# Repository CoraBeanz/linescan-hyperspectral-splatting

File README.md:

<h3 align="center">A homebuilt pushbroom spectrograph rides a robot arm, and the 3D Gaussian splat it trains stores a full 500–950 nm spectrum in every Gaussian instead of an RGB color.</h3>

<p align="center">

</p>

<p align="center">
  <a href="#how-it-works"><b>How it works</b></a> ·
  <a href="#the-rig"><b>The rig</b></a> ·
  <a href="#cad-model"><b>CAD model</b></a> ·
  <a href="#optical-path"><b>Optical path</b></a> ·
  <a href="#optiland-model"><b>Optiland model</b></a> ·
  <a href="#software"><b>Software</b></a> ·
  <a href="#reconstruction"><b>Reconstruction</b></a> ·
  <a href="#roadmap"><b>Roadmap</b></a> ·
  <a href="docs/manual/README.md"><b>User's manual</b></a> ·
  <a href="docs/parts_list_and_design.md"><b>Parts list</b></a>
</p>

## How it works

A hyperspectral camera records a whole spectrum at every pixel instead of three color channels, which shows things RGB can't, like the sharp rise in a leaf's reflectance just past red. This one is built from M12 board lenses, grating film and a Raspberry Pi camera sensor, for under $500 in optics and scanner parts.

| 1 · Pick a viewpoint | 2 · Sweep the slit | 3 · Train the splat |
|---|---|---|
| The SO-101 arm carries the scanner head to a pose and holds still. Its joint angles, through the robot model, give that pose. | A NEMA 8 stepper turns the scan mirror two microsteps per frame. Each frame is one line of the object by its spectrum, and a 107-line sweep covers about 64 × 43 mm. | Every scan line is a training sample. A C++/CUDA renderer draws the splat through a line-camera model at that line's pose and compares it with the measured line. |

## The rig

<table>
  <tr>
    <td width="42%" valign="top">
      
      <br><sub>SO-101 follower arm. Photo: <a href="https://github.com/TheRobotStudio/SO-ARM100">TheRobotStudio/SO-ARM100</a>, Apache-2.0.</sub>
    </td>
    <td valign="top">

**Arm.** An [SO-101](https://huggingface.co/docs/lerobot/so101) follower from [LeRobot](https://github.com/huggingface/lerobot), with six STS3215 servos. It only sets the viewpoint, then holds still while the mirror scans.

**Scanner head.** The spectrograph below, plus a first-surface scan mirror on a 60 g NEMA 8 stepper. A TMC2209 driver runs it at 1/32 microstepping from an ESP32, which takes plain-text commands from the Jetson over USB serial.

**Pose.** The arm's joint readings give the head's pose for every line. A Pi NoIR camera on the head reads a printed ChArUco board once, in the [head calibration](calibration/headcal/README.md), to measure where the head really sits on the wrist.

**Light.** Halogen lamps, because LEDs give almost nothing past 700 nm.

**Compute.** A Jetson Nano for capture, the calibration warp and the CUDA splat renderer.

  </td>
  </tr>
</table>

## CAD model

<table>
  <tr>
    <td width="50%"></td>
    <td width="50%"></td>
  </tr>
  <tr>
    <td><sub>The head from below: scan window and hood, pose camera, NEMA 8 stepper, wrist puck.</sub></td>
    <td><sub>Lid and stepper hidden to show the optical train.</sub></td>
  </tr>
</table>

The whole rig is a parametric [FreeCAD model](cad/). One script builds the SO-101 from its URDF, reads the optical spacings from the Optiland model, and wraps the optics in a printable PETG housing that slides onto a puck on the wrist-roll servo. It checks the parts for clashes, the mirror's full turn and the wrist's clearance, and works out the servo load: the 187 g head needs 75% of the shoulder servo's stall torque with the arm stretched out level, and 18% in the folded scanning pose above. The STLs and assembly steps are in [`cad/`](cad/).

## Optical path

A 16 mm f/4 objective images the object onto a 50 µm slit, so the instrument sees one line at a time. A field lens right behind the slit steers every point of that line toward the camera. A 25 mm lens, used backward, collimates the light, and a 500 lines/mm transmission grating fans it out by wavelength. A 12 mm f/2 lens, tilted 22° to the first diffraction order, refocuses the fan onto an IMX219 NoIR sensor, so each frame is one line of the object by its spectrum. A 500 nm long-pass filter in front keeps second-order light off the near-infrared end. Why each part is there: [final optical train](docs/parts_list_and_design.md#2-final-optical-train-config-c).

### What the camera sees

Each frame is the scan line (vertical) by its spectrum (horizontal), at about 5.8 px per nm. Spectral lines bow slightly across the frame (smile, up to about 33 px at the line ends) and the line length shifts a little with wavelength (keystone, about 11 px). Both get calibrated once with lamp lines and removed by a warp.

## Optiland model

[`optics/spectrograph_model.py`](optics/spectrograph_model.py) builds the whole train in [Optiland](https://github.com/HarrisonKramer/optiland) with ideal thin lenses and traces it. Tracing changed the design twice: the stock Pi NoIR lens was far too small to catch the collimated beam, and without a field lens most of the light from the ends of the line missed the camera lens.

| Config (ideal lenses) | Light at line center | Light at line ends | Dispersion | Spectral resolution | Pixels along the line |
|---|---|---|---|---|---|
| A: stock Pi NoIR v2 lens | 8% | 0% | 1.5 px/nm | 3.7 nm | 543 |
| B: M12 IMX219 + 12 mm f/2 lens | 92–100% | 12–14% | 5.8 px/nm | 3.7 nm | 2,143 |
| **C: B + 18 mm field lens** | **100%** | **98–99%** | **5.8 px/nm** | **4.1 nm** | **2,204** |

Resolution is geometric, with perfect lenses: the slit image's width over the dispersion. For A and B it is the paraxial estimate. For C it is traced through the grating, which widens the slit image 1.08× as the beam leaves at 22°, and the field lens adds 1.03×. The parts that were bought trace to 4.1 nm as [`cad/`](cad/README.md) builds the head, with the field lens curved side to the slit (config E); turned the other way it would be 5.4 nm (config D, [design notes](docs/parts_list_and_design.md#with-the-parts-that-were-bought-configs-d-and-e)). Real M12 lenses will likely land around 5–8 nm. More in the [modeling notes](docs/parts_list_and_design.md#5-modeling-notes-and-limits).

```bash
pip install optiland                   # tested with 0.6.2
python optics/spectrograph_model.py    # prints the table, writes optics/model_output/
python optics/readme_figures.py        # redraws the Optiland figures in docs/img/
```

Full output: [`optics/model_output/results.txt`](optics/model_output/results.txt) and the [ray layouts](optics/model_output/).

## Software

<p align="center">
  <img src="docs/img/software.svg" width="100%" alt="Block diagram of the code. The scan-mirror firmware on the ESP32 talks to the ROS 2 scan arm on the Jetson Nano over USB serial. The camera's frames go to the ROS 2 side during scans and to the calibration kit as lamp frames, and the calibration kit gives the ROS 2 side a wavelength map and a warp. The ROS 2 side passes lines with poses to the line-camera splat, which stores a spectrum in every Gaussian, and the splat goes to a browser viewer as one file. A band at the bottom shows the Optiland and FreeCAD models the code takes its numbers from, and the simulator that renders whole scans from them to test on.">
</p>

The rig isn't built yet, so every module is written and tested against simulated hardware: the firmware on a simulated rig, the ROS 2 side on a fake servo bus and a simulated mirror, the calibration kit on lamp frames rendered through the Optiland model, and the splat on a synthetic scan with known poses. The [instrument simulator](sim/) ties them together: a digital twin of the whole rig that renders complete scan sessions, raw frames and logged poses, from a scene whose spectra and geometry are known. GitHub Actions runs each module's checks on every pull request that touches it.

| Module | What CI checks | Status |
|---|---|---|
| [Scan-mirror firmware](firmware/) | Unit tests on a simulated rig, again under AddressSanitizer and UndefinedBehaviorSanitizer, and the ESP32 build |  |
| [ROS 2 scan arm](ros2/) | `colcon build` and `colcon test` in a ROS 2 Humble container, up to a two-viewpoint scan on mock hardware |  |
| [Calibration kit](calibration/) | The self-test and unit tests on Python 3.10 and 3.13, and the Jetson's capture commands on Python 3.6 and numpy 1.13 against a stand-in camera |  |
| [Line-camera splat](splat/) | CPU build and unit tests, and a small synthetic scan trained end to end; the CUDA build with CUDA 13.4 for a desktop GPU (CI has no GPU, so the GPU tests skip there) |  |
| [Jetson Nano build](jetson/README.md) | The renderer and trainer built with the Nano's CUDA 10.2 and gcc 7.5 for sm_53, every kernel checked against the Nano's registers and shared memory, and the tests on arm64 Ubuntu 18.04 |  |
| [Splat viewer](viewer/) | The page's file reader, colour weights, spectra and WebGL2 image against the C++ renderer, then the page itself at a desktop and a phone size, in headless Chromium |  |
| [GitHub Pages site](https://corabeanz.github.io/linescan-hyperspectral-splatting/) | Builds the front page and the viewer, opens them in headless Chromium, and deploys them from `main` |  |
| [Instrument simulator](sim/) | The self-test, which scans a relief target, calibrates the simulated instrument and checks the reflectance against the truth, and the unit tests, on Python 3.10 with the oldest packages it allows and on 3.13 |  |
| [Virtual first light](pipeline/) | Nightly: a simulated scan through calibration, conversion, training, export and the viewer's reader, each hand-off checked against the simulator's truth |  |
| [CAD model](cad/) | Lint on the FreeCAD scripts |  |
| [PCBs](pcb/) | KiCad's ERC and DRC on the scan-mirror controller and hall-sensor boards, including the check that each board matches its schematic |  |
| [Optiland model](optics/) | Reruns the model and checks that its results, the CAD's as-built optics and the calibration kit's design map are current |  |
| README and docs | The diagrams match the scripts that draw them, and every relative link resolves |  |

Each module's README says how to build and test it locally, and its workflow in [`.github/workflows/`](.github/workflows/) runs the same commands.

### Scan-mirror firmware

An ESP32 runs the mirror from a 50 µs timer interrupt and keeps a line clock that follows the camera's frames. In a stare scan it steps the mirror at each tick, waits for it to settle, and holds it still through the frame; in a sweep scan it turns the mirror at a constant speed and reports its exact position at each tick. Every line, move and hall-sensor edge is stamped in ESP32 microseconds, so each camera frame can be matched to a mirror angle. Homing finds the middle of a hall sensor's window, which repeats to a microstep, and the TMC2209's current and microstepping are set over its UART, with a watchdog that stops the motor on a driver fault.

The Jetson talks to it in [plain-text lines over USB serial](firmware/PROTOCOL.md) rather than micro-ROS, as first planned: there's no agent to run, any serial monitor can drive it, and a ROS 2 node turns it into topics and services. Wiring, first power-up and a bench test with a logic analyser are in [`firmware/`](firmware/).

### ROS 2 scan arm

ROS 2 Humble runs in Docker on the Jetson Nano, since JetPack 4 is Ubuntu 18.04. A ros2_control driver runs the SO-101's STS3215 servos at 100 Hz. For each viewpoint in a plan, `scan_sweep` moves the arm, waits for it to stop, and asks the mirror bridge for a sweep. The bridge maps the ESP32's clock onto ROS time, so each line gets the arm's joint angles at the moment the mirror settled. Through the URDF, which takes the head's geometry from the CAD model, those give the head pose and the line-camera pose: one row per line in `lines.csv`. With mock servos and a simulated mirror the whole stack runs on any Linux machine with Docker, and Foxglove draws every scan line where it lands. The driver also stops the arm on a servo fault, a stall or an e-stop, and keeps the head off the table ([arm safety](ros2/README.md#arm-safety)). Setup on the Nano and first steps with the real arm: [`ros2/`](ros2/README.md).

### Calibration

<p align="center">
  
  <br><sub>A synthetic CFL frame after calibration. On the sensor these lines bow by up to 35 px; here each one is a straight column at its own wavelength.</sub>
</p>

About ten minutes of lamp frames calibrate the spectrograph. A CFL bulb and a neon glow lamp give about 100 lines from 490 to 970 nm, a halogen lamp on PTFE gives the slit's ends and the spectral response, and a red laser pointer checks the result. The calibration kit, `hsical`, fits the wavelength of every pixel, the warp that straightens the bowed lines (smile) and evens out the slit's length across wavelengths (keystone), and the response that turns counts into radiance or reflectance, then writes a report with pass/fail checks. Its capture commands run on the Jetson's stock Python 3.6; the fitting runs on a PC. Before a scan, `hsical check` compares a quick CFL frame with the calibration and says whether anything has moved since.

Without the hardware, it is tested on sessions rendered through the Optiland model from a deliberately imperfect copy of the design: shifted on the sensor, with a denser grating, barrel distortion, dust on the slit, the sensor's colour mosaic and noise. At full resolution it recovers the truth to:

| Error against the truth | Result | Limit |
|---|---|---|
| Wavelength of every pixel, rms | 0.020 nm | 0.10 nm |
| Wavelength of every pixel, worst | 0.070 nm | 0.30 nm |
| Laser wavelength | 0.003 nm | 0.20 nm |
| Reflectance of a test scene, rms | 0.8% | 3% |

First light step by step, and how each fit works: [`calibration/`](calibration/).
Where the head's cameras and mirror really sit on the wrist, measured from one scan of a printed tag board: [`calibration/headcal/`](calibration/headcal/README.md).

### Instrument simulator

<p align="center">
  
  <br><sub>The relief target with every second line of the first sweep, the raw frame of the red line, and the whole sweep as the slit really saw it next to what the calibration kit made of the raw frames.</sub>
</p>

The [simulator](sim/) is a digital twin of the whole scanner: the arm, the scan mirror, the objective and slit, the spectrograph and its camera. Given a scene with known spectra and a scan plan, it renders the raw frame of every scan line and writes a complete session in the rig's own format, with the arm's servo offsets, flex and encoder steps and the mirror's homing error in the log, as the real rig's will have them. Most of it is the repo's own code, imported rather than copied: the URDF's kinematics from the ROS 2 package, the synthetic spectrograph from the calibration kit, and the Optiland design map. Its self-test calibrates the simulated instrument, turns two sweeps of a relief target into reflectance and checks them against the truth: 1.6% RMS reflectance error, and the absorption bands of a rare-earth tile within 0.07 nm.

### On the Jetson Nano

The Nano is stuck on JetPack 4.6: Ubuntu 18.04, CUDA 10.2 and gcc 7. [`jetson/`](jetson/README.md) builds splat for its GPU in a container that uses JetPack's own CUDA, and builds the ROS 2 image in a way JetPack's old Docker can manage. A day-one script builds and tests both and times training on the GPU. From a PC, the same scripts build splat with the Nano's compilers, check that every kernel fits the Nano's registers and shared memory, and run the tests on arm64 Ubuntu 18.04. What training needs on the Nano, in memory and time per dataset, and the commands that measure it: [`splat/docs/nano_budget.md`](splat/docs/nano_budget.md).

## Reconstruction

Published hyperspectral splatting, such as [HyperGS](https://openaccess.thecvf.com/content/CVPR2025/papers/Thirgood_HyperGS_Hyperspectral_3D_Gaussian_Splatting_CVPR_2025_paper.pdf) and [DD-HGS](https://arxiv.org/abs/2505.21890), trains on full multi-view hyperspectral images. Here the splat trains straight from raw scan lines, through a model of the instrument itself.

- **Spectral Gaussians.** Each Gaussian keeps the usual position, shape and opacity, and stores a spectrum over 500–950 nm where a normal splat stores RGB.
- **A line camera, not a pinhole.** The slit only sees a thin fan of rays, and the mirror angle tilts that fan. For each scan line, the renderer draws the splat along that one fan and compares the resulting line of spectra with the measured line.
- **Poses get refined too.** The arm and the tag board give each viewpoint a pose, and the optimizer can adjust those poses along with the Gaussians, so small arm errors don't blur the result.
- **Calibrated input.** Neon and CFL lamp lines fix the wavelength scale, the warp removes smile and keystone, and a white PTFE reference turns counts into reflectance.

Splatting through a non-pinhole camera has precedent in satellite imagery ([RPC-GS](https://arxiv.org/abs/2606.06690)), and close-range pushbroom cameras have been calibrated for plant phenotyping ([Behmann et al. 2015](https://doi.org/10.1016/j.isprsjprs.2015.05.010)). This project puts the two together on hobby hardware.

### Training on a synthetic scan

The renderer and trainer in [`splat/`](splat/) are C++17, with a CUDA rasterizer written for the Nano's CUDA 10.2 and a CPU reference that the tests hold it to. Until there are real scans, they train on a synthetic one: a board with paint patches, a hidden word that only shows past 740 nm, a leaf-green ball and an orange box, scanned through the head's mirror geometry from the CAD model. Each sweep's head pose is off by about 1 mm and 0.3° per axis, as the arm's will be.

The true scene (left), and splats trained from 16 sweeps (middle) and from 8 (right). From 16 sweeps the trainer cuts the pose error from 10.9 px to 0.97 px at 256 px per line, which lines the sweeps up to about 0.15 mm on the board, and it renders the measured lines down to their noise. That takes 16 s on a desktop RTX 4070 SUPER, or under two minutes on a 4-core CPU. From 8 sweeps the ball and the box are seen from too few directions and get painted onto the board, so the rig will scan many sweeps from all around. The model, the CUDA passes and more results are in [`splat/`](splat/).

### In the browser

Every Gaussian carries a spectrum, so the [viewer](viewer/) can draw a trained splat at any single wavelength, in true color, in color infrared, or as a band index such as NDVI, and it plots the full spectrum of any point you click. Above, in color infrared, the ball's leaf spectrum and the black panel's dye both rise past 700 nm, so both turn red and the hidden word shows. It is plain HTML, JavaScript and WebGL2 with no build step, and its tests check it against the C++ renderer. **[Open it in your browser](https://corabeanz.github.io/linescan-hyperspectral-splatting/viewer/)**, on GitHub Pages.

It also shows what each part of the scene is made of: [`splat_materials`](splat/README.md#material-maps) labels every Gaussian by spectral angle against a library of spectra, clusters them and unmixes them, and on the trained splat 97% of the map's pixels get the right material.

## Roadmap

- [x] First-order optical design and Optiland model (configs A, B, C, and D and E with the parts bought)
- [x] [FreeCAD model](cad/) of the arm and scanner head, with printable housing, optics carriers and wrist mount
- [x] [Software](#software), tested in CI against simulated hardware: scan-mirror firmware, ROS 2 scan arm, calibration kit, line-camera splat renderer and trainer, browser viewer, the Jetson Nano build and an instrument simulator
- [ ] **Bench spectrometer:** slit, field lens, collimator, grating and camera aimed at neon and CFL lamps; fit the wavelength map and the smile/keystone warp with the [calibration kit](calibration/)
- [ ] **Line imager and scanner:** add the objective, mirror and stepper together (in the printed head the objective sees out only through the mirror), measure the line on a knife edge, scan a color card, assemble the datacube on the Jetson (first CUDA kernel: warp + bin)
- [ ] **3D:** calibrate the head on the ChArUco board, then scan from several arm viewpoints and train the first splat on real scans

Details for each step are in the [build order](docs/parts_list_and_design.md#4-build-order).

## Stack

| Layer | Built with |
|---|---|
| **Optics** | Python and [Optiland](https://github.com/HarrisonKramer/optiland): ideal-lens model now, catalog lenses next |
| **CAD** | [FreeCAD](https://www.freecad.org/), scripted in Python around the SO-101's URDF |
| **Firmware** | C++ on an ESP32 (Arduino core, PlatformIO) driving a TMC2209, with Unity tests on a simulated rig |
| **Robotics** | ROS 2 Humble in Docker on the Jetson Nano: a ros2_control driver for the STS3215 servos, the URDF and the scan sweeps |
| **Capture and calibration** | Python, numpy and scipy; raw 10-bit frames from the IMX219 NoIR on the Jetson Nano's CSI port, through V4L2 |
| **Reconstruction** | C++17 and CUDA: line-camera Gaussian splat renderer and trainer for the Jetson Nano |
| **Viewer** | Plain HTML, JavaScript and WebGL2, tested in headless Chromium with Playwright |
| **Simulation** | Python and numpy, reusing the calibration kit's and the ROS 2 packages' own code |
| **CI** | GitHub Actions, a workflow per module |

## Repo map

```
docs/
├── parts_list_and_design.md   parts with vendors and prices, first-order design, build order
├── optical_train_v2.svg       optical train drawing (v1 kept alongside)
├── img/                       README figures; img/src/ holds the scripts that draw the SVGs
└── site/                      the GitHub Pages front page, and the script that builds the site
optics/
├── spectrograph_model.py      Optiland model of the spectrograph, configs A–E
├── readme_figures.py          traces the model and renders the Optiland figures
└── model_output/              results.txt and ray layouts
cad/
├── so101_hsi_rig.FCStd        FreeCAD assembly: SO-101 arm and scanner head
├── build_rig.py               builds it, checks clearances and servo load, exports
└── stl/, step/, renders/      printable parts, the head as STEP, images
firmware/
├── lib/scanmirror/            step generator, line clock, commands, homing: plain C++
├── src/main.cpp               the ESP32 glue
├── test/                      Unity tests on a simulated rig
└── PROTOCOL.md                the serial protocol
ros2/
├── so101_scan_*/              ROS 2 Humble packages: driver, URDF, bringup, sweeps, messages
└── docker/, udev/             the container for the Jetson Nano, stable device names
calibration/
├── hsical/                    capture, calibration, reports: python -m hsical
└── tests/                     pytest on synthetic sessions
splat/
├── include/, src/             line-camera renderer (CPU and CUDA) and trainer
├── tools/                     splat_synth, splat_train, splat_render, splat_export
└── tests/                     unit tests; the CUDA ones skip without a GPU
viewer/
├── index.html, js/            the browser viewer: WebGL2, no build step
├── data/                      two splats from the synthetic scan
└── test/                      checks against the C++ renderer, run in headless Chromium
sim/
├── hsisim/                    the instrument simulator: python -m hsisim
└── tests/                     pytest, up to a scan calibrated end to end
jetson/
├── build_all.sh, splat.sh     the Nano's day-one build, splat in its container
├── ros.sh                     the ROS 2 image on JetPack 4.6's Docker
└── check.sh                   the same builds from a PC, with the Nano's compilers
.github/workflows/             CI, a workflow per module
```

## Background reading

- Kerbl et al., [3D Gaussian Splatting for Real-Time Radiance Field Rendering](https://repo-sam.inria.fr/fungraph/3d-gaussian-splatting/), ACM TOG (SIGGRAPH) 2023. [arXiv:2308.04079](https://arxiv.org/abs/2308.04079)
- Thirgood et al., [HyperGS: Hyperspectral 3D Gaussian Splatting](https://openaccess.thecvf.com/content/CVPR2025/papers/Thirgood_HyperGS_Hyperspectral_3D_Gaussian_Splatting_CVPR_2025_paper.pdf), CVPR 2025
- Narayanan et al., [Diffusion-Denoised Hyperspectral Gaussian Splatting](https://arxiv.org/abs/2505.21890) (first posted as *Hyperspectral Gaussian Splatting*), arXiv 2025
- Wagner et al., [RPC-GS: Gaussian Splatting with native RPC Rendering for Satellite Imagery](https://arxiv.org/abs/2606.06690), arXiv 2026
- Behmann et al., [Calibration of hyperspectral close-range pushbroom cameras for plant phenotyping](https://doi.org/10.1016/j.isprsjprs.2015.05.010), ISPRS Journal of Photogrammetry and Remote Sensing 106, 2015

## Credits

- SO-101 photo: [TheRobotStudio/SO-ARM100](https://github.com/TheRobotStudio/SO-ARM100) (`media/SO101_Follower.webp`), used unmodified under the Apache License 2.0; a copy of the license is in [`docs/img/SO-ARM100_LICENSE.txt`](docs/img/SO-ARM100_LICENSE.txt). The SO-101 is designed by The Robot Studio in collaboration with Hugging Face.
- SO-101 URDF and meshes in the CAD model: [TheRobotStudio/SO-ARM100](https://github.com/TheRobotStudio/SO-ARM100) (`Simulation/SO101`), Apache License 2.0.
- Ray tracing: [Optiland](https://github.com/HarrisonKramer/optiland) (MIT).

## License

The code, the CAD model and the docs are under the [MIT License](LICENSE). The SO-101's URDF and meshes (and their decimated copies in the CAD model) and the SO-101 photo are TheRobotStudio's, under the Apache License 2.0, as listed in [Credits](#credits).

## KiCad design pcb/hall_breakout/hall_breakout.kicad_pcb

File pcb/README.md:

# PCBs

Two boards, drawn in KiCad 10. Everything else on the rig is a ready-made module, a ribbon or a USB cable.

| Board | What it does | Size | Order with |
|---|---|---|---|
| [Scan-mirror controller](#scan-mirror-controller) | Carries the ESP32-DevKitC and the BTT TMC2209 in sockets, takes 12 V for the mirror's NEMA 8, and has the motor, hall-sensor and Jetson connectors | 95 × 66 mm, 2 layers, 1.6 mm | [`scan_controller/fab/`](scan_controller/fab/) |
| [Hall-sensor breakout](#hall-sensor-breakout) | Holds the A3144 home sensor's leads on the outside of the scanner head and takes its 3-wire cable | 14 × 12.4 mm, 2 layers, 0.8 mm | [`hall_breakout/fab/`](hall_breakout/fab/) |

Both boards pass KiCad's electrical rules check (ERC) and design rules check (DRC) with no errors or warnings, including the check that each board matches its schematic. CI runs both on every pull request that touches `pcb/` ([`pcb.yml`](../.github/workflows/pcb.yml)).

## Before you order

1. **Which ESP32 board you have.** The controller's socket is for the **38-pin ESP32-DevKitC**: two rows of 19 pins, **25.4 mm (1.0 in) apart**, with 3V3 and GND at the antenna end. Measure your board's rows. If it's the 30-pin DOIT DevKit, or a 38-pin board with rows 22.9 mm apart, the socket has to change before you order. Its module must be an **ESP32-WROOM-32** (any of -32, -32D, -32E, -32U, -32UE), as on the DevKitC-32E. Not an ESP32-SOLO-1: it has one core, and the firmware needs two. Don't use a **WROVER** module (DevKitC-VE or -VIE): those use GPIO 16 and 17 for their PSRAM, and this board uses them for the TMC2209's UART.
2. **The driver's pinout.** Look at your TMC2209 from the potentiometer side, potentiometer at the top. The left header should read, from the top, EN, MS1, MS2, RX, TX, CLK, STEP, DIR on BTT's V1.3, or EN, MS1, MS2, PDN, PDN, CLK, STEP, DIR on the V1.2. The right header should read VS (VM on the V1.2), GND, A2, A1, B1, B2, VIO (VDD), GND. The board's silkscreen marks EN and VM.
3. **Which pin carries the UART.** BTT ships the TMC2209 with the UART on its 4th pin (RX on the V1.3), and this board's solder jumper JP1 comes bridged for that (pads 1-2). The 5th pin (TX) only connects if you fit the module's R10. If your module was changed to use it, cut the thin bridge between JP1's pads 1 and 2 and solder 2 to 3.
4. **The barrel jack's pins.** The footprint is KiCad's generic 5.5 × 2.1 mm jack (the common DC-005 style): centre pin at the back, sleeve pin 6 mm in front of it, switch pin 4.7 mm to the side. Check your jack against that, or buy a DC-005.
5. **The 100 µF capacitor** you already have needs to be a radial can, 6.3 mm across, with leads 2.5 mm apart.
6. **At JLCPCB, check the placement preview** for the four parts with a direction: D1 and D2 (cathode stripe toward the left, toward the TMC2209), and LEDs D3 and D4 (cathode mark on the left).

## Scan-mirror controller

[Schematic (PDF)](scan_controller/fab/scan_controller.pdf) · [KiCad project](scan_controller/scan_controller.kicad_pro)

It sits beside the SO-101's base. Its wiring is the firmware's pin map ([`board_pins.h`](../firmware/include/board_pins.h)) made permanent: the [firmware README](../firmware/README.md#wiring) describes the same circuit on a breadboard.

- **ESP32-DevKitC (U1)** in two 1×19 female headers, USB toward the board's top edge. It's powered and commanded over its USB cable to the Jetson. Espressif says to power the DevKitC from only one source (USB, its 5V pin or its 3V3 pin), so the board takes its 5 V and 3.3 V from the DevKit and has **no regulator of its own**. A side effect is a safety feature: with USB unplugged the TMC2209 has no logic supply, so the motor can't move even with 12 V on.
- **Status LED D4** on GPIO 2, through R8 (1 k). The firmware drives it: off when the motor is disabled, on when it's enabled, blinking on a driver fault. A genuine DevKitC has no LED on that pin; many clones have a blue one there. GPIO 2 must be low or floating while the ESP32 boots, and the LED to GND keeps it that way, as on those clones.
- **BTT TMC2209 (U2)** in two 1×8 female headers, wired for UART mode. STEP, DIR and EN go to GPIO 26, 25 and 27. R1 (10 k) pulls EN to 3.3 V, so the motor stays off while the ESP32 boots. The single-wire UART goes to PDN: RX (GPIO 16) straight to it, TX (GPIO 17) through R3 (1 k), because the ESP32 and the driver take turns driving that one wire. MS1 and MS2 go to GND (UART address 0) and CLK to GND (the driver's own clock). VDD is the DevKit's 3.3 V.
- **12 V in** on J1 (the ALITOVE's 5.5 × 2.1 mm plug) or J2 (screw terminal, for a bench supply). F1, a 0.5 A resettable fuse, limits what the 3 A supply can push into a fault. D1 (SS34 Schottky) blocks a reversed supply. D2 (SMAJ15A TVS) clamps spikes when the supply is plugged in or the motor stops, keeping them under the TMC2209's 29 V limit. C1 (100 µF) and C2 (100 nF) sit next to the driver's VM pin. D3 lights while the motor has power.
- **Hall sensor** on J4: 5 V from the DevKit's 5V pin, GND, and the sensor's output. That pin is the USB supply after a Schottky diode, so it reads about 4.7 V; the A3144 needs at least 4.5 V. Its open-collector output can only pull low, so R2 pulls it up to 3.3 V and the ESP32 never sees 5 V. R4 (1 k) limits the current into GPIO 33 if the cable is ever wired wrong. C3 (1 nF) is left off; fit it if motor noise shows up on the hall line.
- **Jetson** on J5: MOVING (GPIO 18) and TRIG (GPIO 19), each through 220 Ω, and GND. Both sides are 3.3 V, so no level shifting. No code reads these pins yet; scan timing comes over the serial link.

### Connectors

| | Type | Pins | Goes to |
|---|---|---|---|
| J1 | 5.5 × 2.1 mm DC jack | centre +12 V | ALITOVE 12 V 3 A supply |
| J2 | 2-pin screw terminal, 5.08 mm | `+` 12 V, `-` GND | a bench supply instead of J1 |
| J3 | JST XH, 4-pin | 1 A2, 2 A1, 3 B1, 4 B2 | NEMA 8: one coil on pins 1-2, the other on 3-4 |
| J4 | JST XH, 3-pin | 1 +5 V, 2 GND, 3 OUT | hall breakout's cable (same pin order there) |
| J5 | 1×3 pin header, 2.54 mm | 1 MOVING, 2 TRIG, 3 GND | free GPIO inputs on the Jetson's 40-pin header, or a scope |
| U1 | DevKit's micro-USB | | Jetson (power and serial) |

Find the motor's coil pairs with a multimeter, not by wire colour: about 24 Ω within a coil, open between coils. A coil connected the wrong way round only reverses the direction, which `CFG dir_inv=1` undoes.

### Before the first power-up

1. **Turn the current down.** BTT's modules leave the factory at VREF ≈ 1.2 V, about 0.85 A, four times what the NEMA 8 takes. With the driver in its socket, **the motor unplugged** and 12 V on, measure between the potentiometer and GND (J5 pin 3 or J2 `-`) and turn it to **VREF ≈ 0.28 V (0.2 A)**. The firmware sets the current over UART, but VREF is what the driver uses before that.
2. **Never plug or unplug the motor while D3 is lit.** The spike can kill the driver. D4, the status LED, stays off until the firmware runs `ENABLE`.
3. Check the EN pull-up: hold the DevKit's EN button and the driver's EN pin (U2 pin 1) should read 3.3 V.

The firmware README covers the [same steps](../firmware/README.md#before-the-first-power-up). For the [bench test without the motor](../firmware/README.md#bench-test-without-the-motor), leave the TMC2209 out: its empty socket takes male jumper wires for the logic analyser (EN on U2 pin 1, STEP on 7, DIR on 8), and MOVING, TRIG and GND are on J5.

### Outline for the base tray

Coordinates in mm from the board's top-left corner, x to the right and y down, with the USB edge at the top and 12 V at the right:

- **Outline:** 95.0 × 66.0 mm, corners rounded to 2 mm, 1.6 mm thick.
- **Mounting holes:** four M3 (3.2 mm) at (3.5, 3.5), (91.5, 3.5), (3.5, 62.5) and (91.5, 62.5). Through-hole leads stick out up to 3 mm underneath, so stand the board off at least 4 mm.
- **Openings:**
  - Micro-USB: top edge, centred at x 26.7, about 14 mm above the board.
  - 12 V jack: right edge, centred at y 14.0, about 6 mm above the board.
  - Screw terminal's wire entries: right edge at y 22.9 and 28.0.
  - J5: a vertical header at x 2.5, y 33.0 to 38.1, near the left edge. Its jumper wires leave upward and stand about 20 mm tall with Dupont housings.
  - J3 and J4 are vertical, so their cables leave upward: J3 at x 66.0, y 20.3 to 27.8; J4 at y 61.0, x 45.7 to 50.7.
- **Heights:** the TMC2209 and its heatsink reach about 22 mm above the board, the DevKit about 16 mm, the screw terminal about 14 mm with its screws on top, and everything else 11 mm or less. Leave air over the driver.

## Hall-sensor breakout

[Schematic (PDF)](hall_breakout/fab/hall_breakout.pdf) · [KiCad project](hall_breakout/hall_breakout.kicad_pro)

The A3144 sits in its pocket in the head's +X wall ([`cad/`](../cad/README.md)), printed face toward the magnet. Its leads leave the bottom of the body, bend 90° toward the outside just below it, run out through the wall's slot, and pass through this board from the back. The board lies flat on the outside of the wall and is held by the soldered leads and a dot of CA glue, or by an M2 screw. C1 (100 nF) bypasses the sensor's supply right at its leads, which matters here because the cable runs up the arm next to the motor's. The pull-up is on the controller.

Seen from outside the head, the leads run **OUT, GND, VCC from left to right**, mirrored from the datasheet's front view, because you're looking at the sensor's back. The square pad is VCC. The cable solders into the three pads marked S, G and + (OUT, GND, +5 V), in the controller's J4 order. The two 1.5 mm holes below them are for strain relief: tie the cable to the board with thread through both holes before you mount it, since the board lies flat on the wall. Even miniature cable ties (about 2.5 mm wide) won't fit through. Solder the cable straight in rather than fitting a pin header, which would stand about 9 mm off the head.

**Where it goes**, in the head's frame (mm): the +X outer face is at x = 16.0. Bent under the body, the leads come out at about z = 21.2, at y = −11.54 (OUT), −10.27 (GND) and −9.00 (VCC). The board follows the leads: it spans y −17.27 to −3.27 and z 13.4 to 25.8, clear of the lid-bolt counterbores below it. Its M2 hole is at y −15.47, z 20.8, where an M2 × 5 screwed into the wall clears the mirror clamp by 1.1 mm, and the tie holes are at y −14.87 and −5.67, z 15.2. It stands about 2 mm proud of the wall, or 3 mm with the cable.

### In the CAD

- The [controller tray](../cad/README.md#controller-tray) and the hall breakout are in [`cad/`](../cad/README.md). The A3144's leads leave the bottom of its body and run out through a slot under its pocket, and the breakout sits on them as above.
- The head's M2 pilot hole for the breakout has to sit under the board's hole, at y −15.47, z 20.8.
- Still to add: cable clips along the arm for the 4-wire motor cable and the 3-wire hall cable. Keep them apart, and give the hall cable strain relief at the head.

## Parts

Parts you already have go in sockets or are soldered by hand. JLCPCB's SMT assembly fits the small parts, all on the top side. Every part number below was checked on [LCSC](https://www.lcsc.com/) in October 2026.

| Ref | Part | Who fits it |
|---|---|---|
| U1 | ESP32-DevKitC (yours), in 2 × 1×19 female headers, 2.54 mm | you |
| U2 | BTT TMC2209 V1.3 (yours), in 2 × 1×8 female headers, 2.54 mm | you |
| C1 | 100 µF 25 V electrolytic (yours; 35 V is better), 6.3 mm, 2.5 mm pitch | you |
| J1 | 5.5 × 2.1 mm DC jack, DC-005 style | you |
| J2 | 2-pin screw terminal, 5.08 mm (KF301-5.08 or Phoenix MKDS 1,5/2-5,08) | you |
| J3 | JST B4B-XH-A, LCSC C144395, plus a 4-pin XH pigtail for the motor | you |
| J4 | JST B3B-XH-A, LCSC C144394, plus a 3-pin XH pigtail for the hall cable | you |
| J5 | 1×3 pin header, 2.54 mm | you |
| F1 | 0.5 A hold, 30 V PTC fuse, 1812: PTTC SMD1812P050TF/30, C492015 | JLCPCB |
| D1 | SS34 Schottky, SMA: C8678 | JLCPCB |
| D2 | SMAJ15A TVS, SMA: C113958 | JLCPCB |
| D3 | green LED, 0805: KT-0805G, C2297 | JLCPCB |
| D4 | red LED, 0805: NCD0805R1, C84256 | JLCPCB |
| C2 | 100 nF 50 V X7R, 0805: C49678 | JLCPCB |
| C3 | 1 nF 0805, C46653: not fitted | |
| R1, R2 | 10 k 0805: C17414 | JLCPCB |
| R3, R4, R8 | 1 k 0805: C17513 | JLCPCB |
| R5, R6 | 220 Ω 0805: C17557 | JLCPCB |
| R7 | 4.7 k 0805: C17673 | JLCPCB |
| hall U1 | A3144 (yours) | you |
| hall C1 | 100 nF 0805, C49678 (large pads, easy to hand-solder) | you or JLCPCB |

The ALITOVE supply, the NEMA 8 and the magnet need no board parts. Keep your through-hole 10 k and 1 k resistors for breadboard tests; the boards use 0805s. F1 and D2 may be "extended" parts at JLCPCB, which adds a small fee per part type; they're easy to hand-solder instead.

## Ordering at JLCPCB

**Controller:** upload [`scan_controller_gerbers.zip`](scan_controller/fab/scan_controller_gerbers.zip). Use the defaults (2 layers, FR-4, 1.6 mm, 1 oz copper, any solder mask colour). The default finish is leaded HASL; pick LeadFree HASL if you want lead-free. The board uses 0.25 mm tracks, 0.2 mm clearance and 0.3 mm vias, all standard. For assembly, choose economic PCBA on the top side and upload [`bom_jlc.csv`](scan_controller/fab/bom_jlc.csv) and [`cpl_jlc.csv`](scan_controller/fab/cpl_jlc.csv), which cover only the parts JLCPCB fits. [`bom.csv`](scan_controller/fab/bom.csv) lists everything.

**Hall breakout:** upload [`hall_breakout_gerbers.zip`](hall_breakout/fab/hall_breakout_gerbers.zip) and set the thickness to **0.8 mm**, which keeps it close to the wall. Everything else stays default. With one capacitor on it, assembly is optional ([`bom_jlc.csv`](hall_breakout/fab/bom_jlc.csv), [`cpl_jlc.csv`](hall_breakout/fab/cpl_jlc.csv)). JLCPCB prints an order number on each board unless you pay to remove it; on a board this small it may land on the back, which is fine.

## Files

```
pcb/
├── README.md
├── lib/                   project library: rig.kicad_sym and rig.pretty
├── scan_controller/       KiCad project (.kicad_pro, .kicad_sch, .kicad_pcb)
│   └── fab/               gerbers and drill (zip), BOMs, placement file, schematic PDF, ERC and DRC reports
├── hall_breakout/         same layout
├── img/                   the renders above
└── tools/
    ├── boards.py          each board's parts, nets, placement and track routes
    ├── build_boards.py    writes the library, schematics and layouts from boards.py
    ├── fab.py             ERC, DRC and the fab files
    ├── library.py         the project library, and the parts KiCad doesn't have
    ├── schematic.py       schematic writer
    └── sexpr.py           reads and writes KiCad's file format
```

The library holds copies of the KiCad parts the boards use, plus six footprints drawn here: the ESP32-DevKitC socket, the TMC2209 socket, the A3144's lead holes, the cable pads, the 1.5 mm tie hole and the M2 hole. It also has three symbols drawn here: the DevKitC, the TMC2209 and the A3144. So the projects open the same way on any machine, and in CI, whatever KiCad libraries are installed.

## Editing and rebuilding

Open `scan_controller/scan_controller.kicad_pro` or `hall_breakout/hall_breakout.kicad_pro` in KiCad 10 and edit as usual. Then refresh the fab files and renders:

```bash
python pcb/tools/fab.py                 # ERC, DRC, then fab/ and img/ for both boards
python pcb/tools/fab.py --check-only    # ERC and DRC only, as CI runs them
```

The boards were generated by `build_boards.py`, which places and routes every part from `boards.py`. It needs the Python that ships with KiCad, which has the `pcbnew` module, and it **overwrites both projects**: rerun it only after changing `boards.py` or `library.py`, not after editing a board by hand. A 30-pin DevKit, for example, needs a new socket and symbol in `library.py` and new pad numbers in `boards.py`.

```bash
"%LOCALAPPDATA%\Programs\KiCad\10.0\bin\python.exe" pcb\tools\build_boards.py    # Windows
```

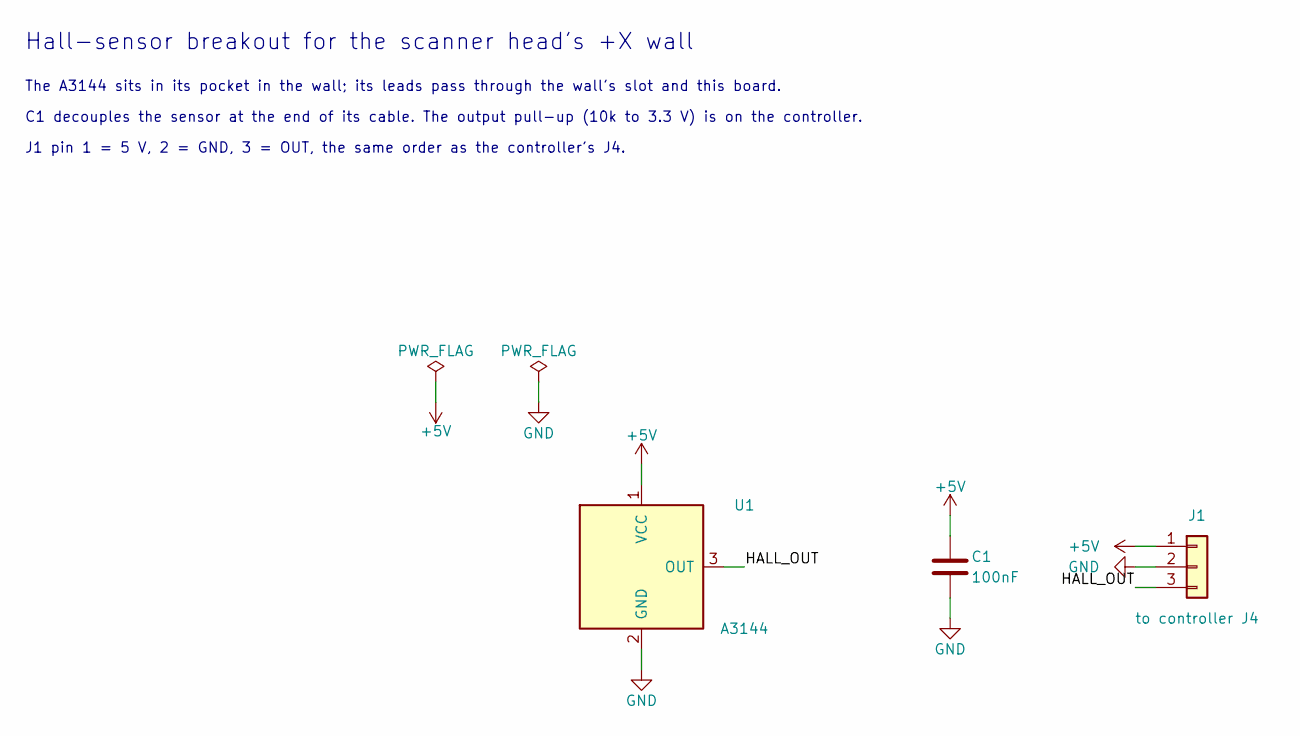
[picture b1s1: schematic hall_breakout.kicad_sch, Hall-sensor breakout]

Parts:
C1: 100nF; C_0805_2012Metric_Pad1.18x1.45mm_HandSolder; MPN YAGEO CC0805KRX7R9BB104; LCSC C49678
J1: to controller J4; Wire_Pads_1x03_P2.54mm; MPN 3-wire cable soldered in (or a 1x3 pin 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
U1: A3144; A3144_UA_Leads; MPN Allegro A3144 (Gikfun), UA package

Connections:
+5V: C1.1, J1.1, U1.1 (VCC)
/HALL_OUT: J1.3, U1.3 (OUT)
GND: C1.2, J1.2, U1.2 (GND)

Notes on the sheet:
C1 decouples the sensor at the end of its cable. The output pull-up (10k to 3.3 V) is on the controller.
The A3144 sits in its pocket in the wall; its leads pass through the wall's slot and this board.
Hall-sensor breakout for the scanner head's +X wall
J1 pin 1 = 5 V, 2 = GND, 3 = OUT, the same order as the controller's J4.

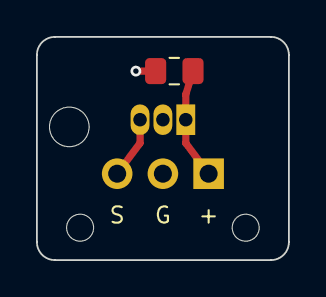
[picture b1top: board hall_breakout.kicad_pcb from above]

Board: 2 copper layers, 14.0 x 12.4 mm, 6 parts (0 on the bottom side), 3 nets.

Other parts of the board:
H1: M2; Hole_M2_2.2mm
H2, H3: tie; Hole_NPTH_1.5mm

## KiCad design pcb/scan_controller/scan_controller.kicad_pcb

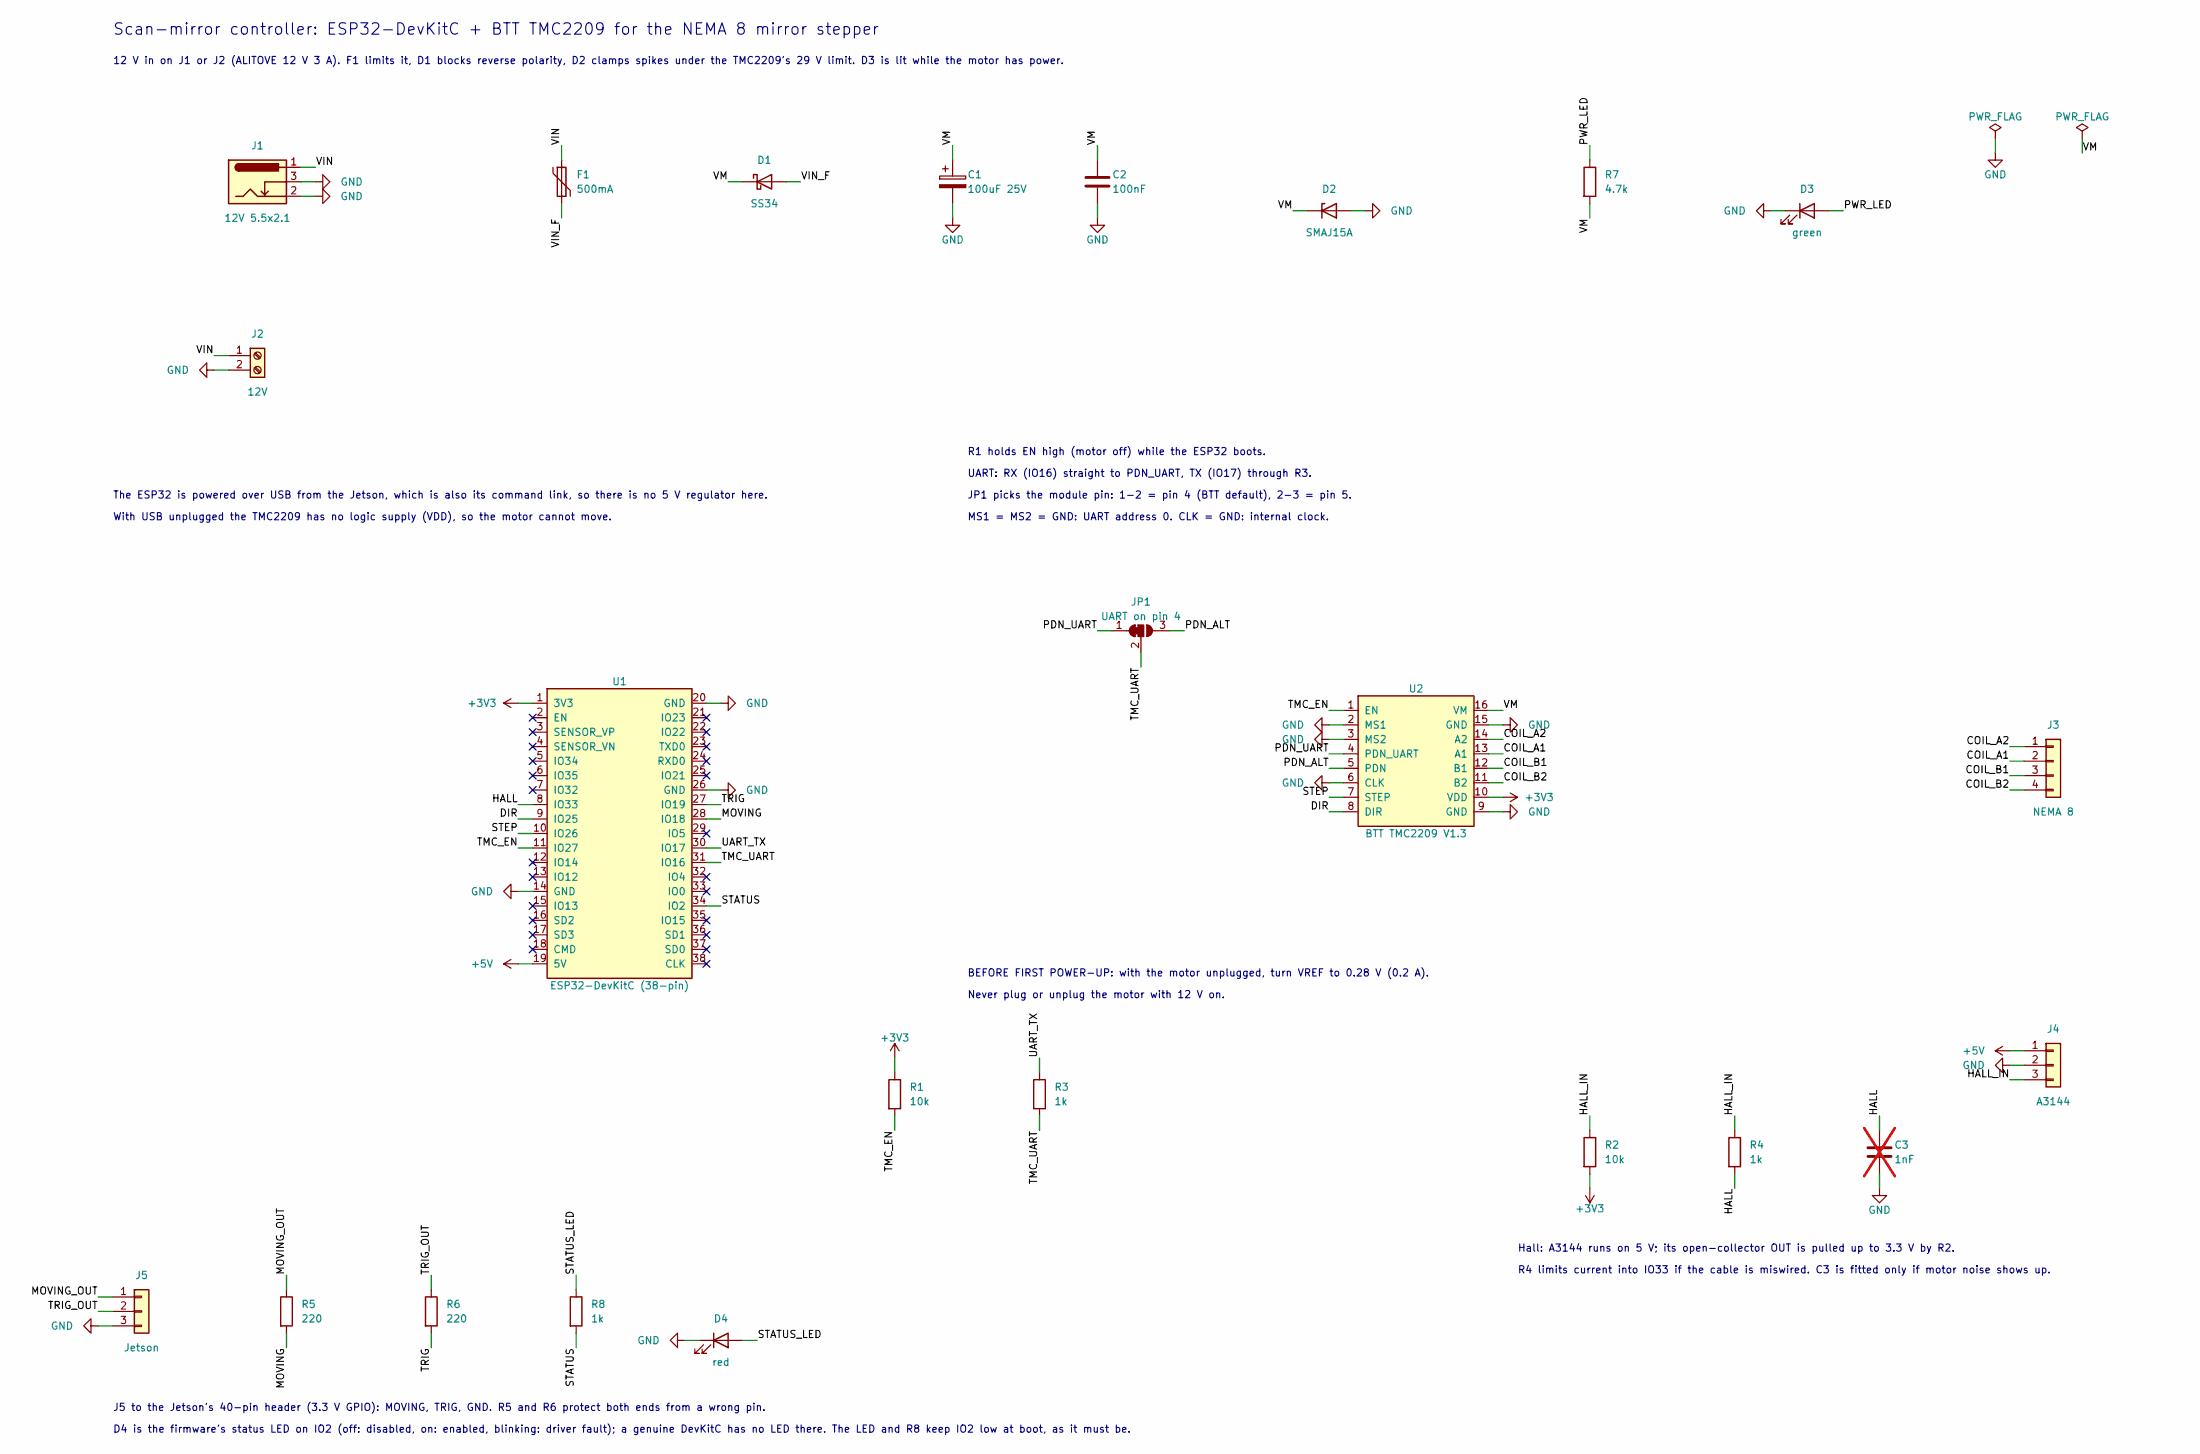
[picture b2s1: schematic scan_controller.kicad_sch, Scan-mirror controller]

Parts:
C1: 100uF 25V; CP_Radial_D6.3mm_P2.50mm; MPN 100 uF 25 V or 35 V electrolytic, 6.3 m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
C2: 100nF; C_0805_2012Metric; MPN YAGEO CC0805KRX7R9BB104; LCSC C49678
C3: 1nF; C_0805_2012Metric; MPN Samsung CL21B102KBCNNNC; LCSC C46653; not fitted
D1: SS34; D_SMA; MPN MDD SS34; LCSC C8678
D2: SMAJ15A; D_SMA; MPN MDD SMAJ15A; LCSC C113958
D3: green; LED_0805_2012Metric; MPN Hubei KENTO KT-0805G; LCSC C2297
D4: red; LED_0805_2012Metric; MPN NATIONSTAR NCD0805R1; LCSC C84256
F1: 500mA; Fuse_1812_4532Metric; MPN PTTC SMD1812P050TF/30; LCSC C492015
J1: 12V 5.5x2.1; BarrelJack_Horizontal; MPN DC-005 style 5.5 x 2.1 mm jack, 3 pins
J2: 12V; TerminalBlock_Phoenix_MKDS-1,5-2-5.08_1x02_P5.08mm_Horizont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; MPN 2-pin screw terminal, 5.08 mm (KF301-5.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
J3: NEMA 8; JST_XH_B4B-XH-A_1x04_P2.50mm_Vertical; MPN JST B4B-XH-A(LF)(SN); LCSC C144395
J4: A3144; JST_XH_B3B-XH-A_1x03_P2.50mm_Vertical; MPN JST B3B-XH-A(LF)(SN); LCSC C144394
J5: Jetson; PinHeader_1x03_P2.54mm_Vertical; MPN 1x3 pin header, 2.54 mm
JP1: UART on pin 4; SolderJumper-3_P1.3mm_Bridged12_RoundedPad1.0x1.5mm_NumberL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
R1, R2: 10k; R_0805_2012Metric; MPN UNI-ROYAL 0805W8F1002T5E; LCSC C17414
R3, R4, R8: 1k; R_0805_2012Metric; MPN UNI-ROYAL 0805W8F1001T5E; LCSC C17513
R5, R6: 220; R_0805_2012Metric; MPN UNI-ROYAL 0805W8F2200T5E; LCSC C17557
R7: 4.7k; R_0805_2012Metric; MPN UNI-ROYAL 0805W8F4701T5E; LCSC C17673
U1: ESP32-DevKitC (38-pin); ESP32-DevKitC_Socket; MPN 2x female header 1x19, 2.54 mm (ESP32-D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
U2: BTT TMC2209 V1.3; StepStick_Socket_BTT_TMC2209; MPN 2x female header 1x8, 2.54 mm (driver p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

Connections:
+3V3: R1.1, R2.2, U1.1 (3V3), U2.10 (VDD)
+5V: J4.1, U1.19 (5V)
/COIL_A1: J3.2, U2.13 (A1)
/COIL_A2: J3.1, U2.14 (A2)
/COIL_B1: J3.3, U2.12 (B1)
/COIL_B2: J3.4, U2.11 (B2)
/DIR: U1.9 (IO25), U2.8 (DIR)
/HALL: C3.1, R4.2, U1.8 (IO33)
/HALL_IN: J4.3, R2.1, R4.1
/MOVING: R5.2, U1.28 (IO18)
/MOVING_OUT: J5.1, R5.1
/PDN_ALT: JP1.3 (B), U2.5 (PDN)
/PDN_UART: JP1.1 (A), U2.4 (PDN_UART)
/PWR_LED: D3.2 (A), R7.1
/STATUS: R8.2, U1.34 (IO2)
/STATUS_LED: D4.2 (A), R8.1
/STEP: U1.10 (IO26), U2.7 (STEP)
/TMC_EN: R1.2, U1.11 (IO27), U2.1 (EN)
/TMC_UART: JP1.2 (C), R3.2, U1.31 (IO16)
/TRIG: R6.2, U1.27 (IO19)
/TRIG_OUT: J5.2, R6.1
/UART_TX: R3.1, U1.30 (IO17)
/VIN: F1.1, J1.1, J2.1
/VIN_F: D1.2 (A), F1.2
/VM: C1.1, C2.1, D1.1 (K), D2.1 (K), R7.2, U2.16 (VM)
GND: C1.2, C2.2, C3.2, D2.2 (A), D3.1 (K), D4.1 (K), J1.2, J1.3, J2.2, J4.2, J5.3, U1.14 (GND), U1.20 (GND), U1.26 (GND), U2.2 (MS1), U2.3 (MS2), U2.6 (CLK), U2.9 (GND), U2.15 (GND)

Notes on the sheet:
J5 to the Jetson's 40-pin header (3.3 V GPIO): MOVING, TRIG, GND. R5 and R6 protect both ends from a wrong pin.
JP1 picks the module pin: 1-2 = pin 4 (BTT default), 2-3 = pin 5.
12 V in on J1 or J2 (ALITOVE 12 V 3 A). F1 limits it, D1 blocks reverse polarity, D2 clamps spikes under the TMC2209's 29 V limit. D3 is lit while the motor has power.
D4 is the firmware's status LED on IO2 (off: disabled, on: enabled, blinking: driver fault); a genuine DevKitC has no LED there. The LED and R8 keep IO2 low at boot, as it must be.
The ESP32 is powered over USB from the Jetson, which is also its command link, so there is no 5 V regulator here.
With USB unplugged the TMC2209 has no logic supply (VDD), so the motor cannot move.
BEFORE FIRST POWER-UP: with the motor unplugged, turn VREF to 0.28 V (0.2 A).
MS1 = MS2 = GND: UART address 0. CLK = GND: internal clock.
Never plug or unplug the motor with 12 V on.
Scan-mirror controller: ESP32-DevKitC + BTT TMC2209 for the NEMA 8 mirror stepper
UART: RX (IO16) straight to PDN_UART, TX (IO17) through R3.
R4 limits current into IO33 if the cable is miswired. C3 is fitted only if motor noise shows up.
Hall: A3144 runs on 5 V; its open-collector OUT is pulled up to 3.3 V by R2.
R1 holds EN high (motor off) while the ESP32 boots.

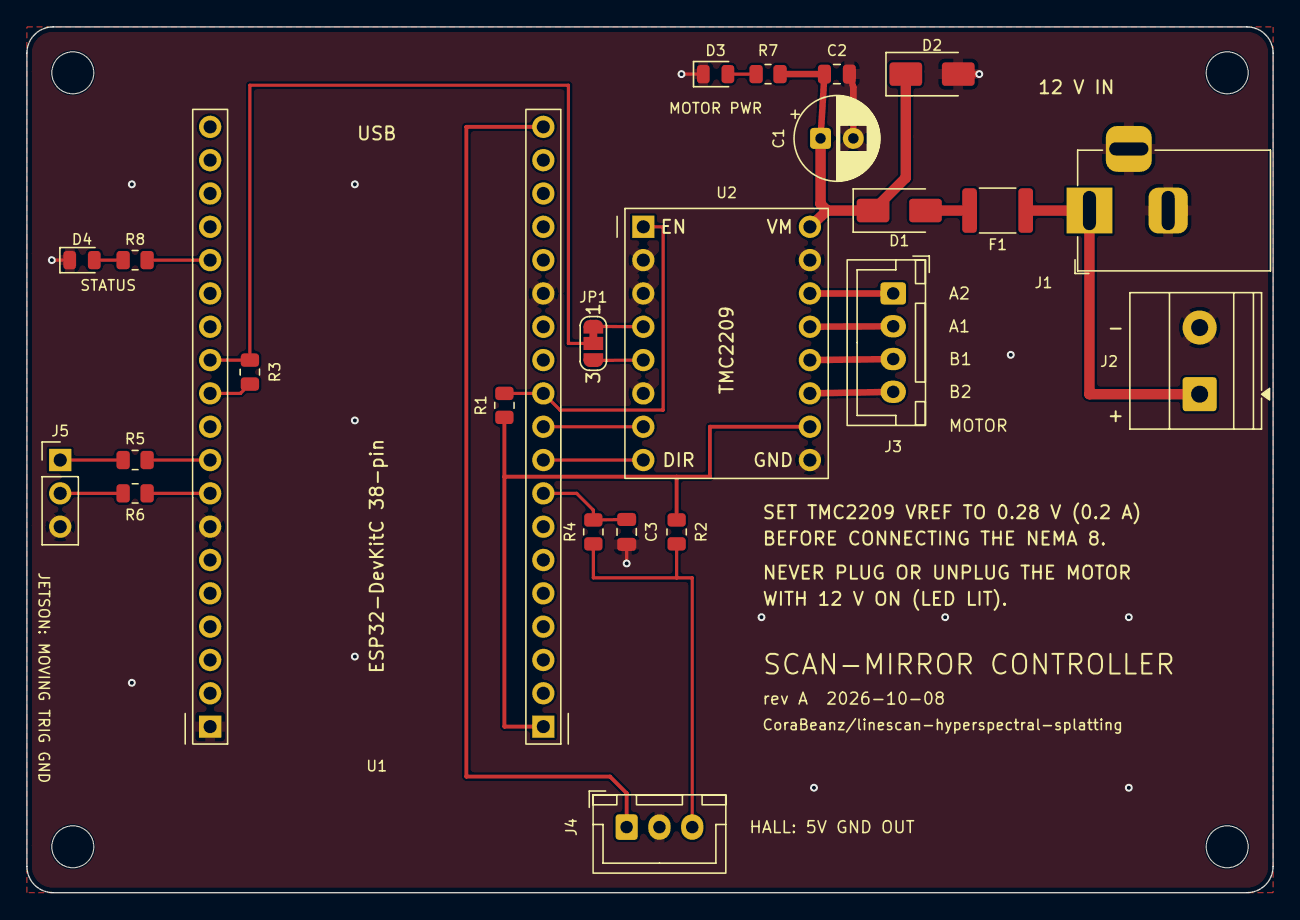
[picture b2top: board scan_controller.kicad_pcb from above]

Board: 2 copper layers, 95.0 x 66.0 mm, 28 parts (0 on the bottom side), 26 nets.

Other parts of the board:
H1, H2, H3, H4: M3; MountingHole_3.2mm_M3

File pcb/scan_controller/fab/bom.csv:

Designator,Value,Footprint,Qty,LCSC,MPN,Assembly,DNP
C1,100uF 25V,rig:CP_Radial_D6.3mm_P2.50mm,1,,"100 uF 25 V or 35 V electrolytic, 6.3 mm, 2.5 mm pitch",hand,
C2,100nF,rig:C_0805_2012Metric,1,C49678,YAGEO CC0805KRX7R9BB104,JLC,
C3,1nF,rig:C_0805_2012Metric,1,C46653,Samsung CL21B102KBCNNNC,JLC,DNP
D1,SS34,rig:D_SMA,1,C8678,MDD SS34,JLC,
D2,SMAJ15A,rig:D_SMA,1,C113958,MDD SMAJ15A,JLC,
D3,green,rig:LED_0805_2012Metric,1,C2297,Hubei KENTO KT-0805G,JLC,
D4,red,rig:LED_0805_2012Metric,1,C84256,NATIONSTAR NCD0805R1,JLC,
F1,500mA,rig:Fuse_1812_4532Metric,1,C492015,PTTC SMD1812P050TF/30,JLC,
J1,12V 5.5x2.1,rig:BarrelJack_Horizontal,1,,"DC-005 style 5.5 x 2.1 mm jack, 3 pins",hand,
J2,12V,"rig:TerminalBlock_Phoenix_MKDS-1,5-2-5.08_1x02_P5.08mm_Horizontal",1,,"2-pin screw terminal, 5.08 mm (KF301-5.08 or Phoenix MKDS 1,5/2-5,08)",hand,
J3,NEMA 8,rig:JST_XH_B4B-XH-A_1x04_P2.50mm_Vertical,1,C144395,JST B4B-XH-A(LF)(SN),hand,
J4,A3144,rig:JST_XH_B3B-XH-A_1x03_P2.50mm_Vertical,1,C144394,JST B3B-XH-A(LF)(SN),hand,
J5,Jetson,rig:PinHeader_1x03_P2.54mm_Vertical,1,,"1x3 pin header, 2.54 mm",hand,
"R1,R2",10k,rig:R_0805_2012Metric,2,C17414,UNI-ROYAL 0805W8F1002T5E,JLC,
"R3,R4,R8",1k,rig:R_0805_2012Metric,3,C17513,UNI-ROYAL 0805W8F1001T5E,JLC,
"R5,R6",220,rig:R_0805_2012Metric,2,C17557,UNI-ROYAL 0805W8F2200T5E,JLC,
R7,4.7k,rig:R_0805_2012Metric,1,C17673,UNI-ROYAL 0805W8F4701T5E,JLC,
U1,ESP32-DevKitC (38-pin),rig:ESP32-DevKitC_Socket,1,,"2x female header 1x19, 2.54 mm (ESP32-DevKitC plugs in)",hand,
U2,BTT TMC2209 V1.3,rig:StepStick_Socket_BTT_TMC2209,1,,"2x female header 1x8, 2.54 mm (driver plugs in)",hand,

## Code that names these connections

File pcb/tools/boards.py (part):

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    ("J4", "Conn_01x03", "A3144", "rig:JST_XH_B3B-XH-A_1x03_P2.50mm_Vertical",
     {"1": "+5V", "2": "GND", "3": "HALL_IN"}, XH3, (365.76, 205.74), {}),
    ("J5", "Conn_01x03", "Jetson", "rig:PinHeader_1x03_P2.54mm_Vertical",
     {"1": "MOVING_OUT", "2": "TRIG_OUT", "3": "GND"}, hand("1x3 pin header, 2.54 mm"), (30.48, 248.92), {}),
]

CONTROLLER_FLAGS = [("GND", 355.6, 43.18), ("VM", 370.84, 43.18)]
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    (271.78, 238.76, 1.27, "Hall: A3144 runs on 5 V; its open-collector OUT is pulled up to 3.3 V by R2."),
    (271.78, 242.57, 1.27, "R4 limits current into IO33 if the cable is miswired. "
                           "C3 is fitted only if motor noise shows up."),
    (25.4, 266.7, 1.27, "J5 to the Jetson's 40-pin header (3.3 V GPIO): MOVING, TRIG, GND. "
                        "R5 and R6 protect both ends from a wrong pin."),
    (25.4, 270.51, 1.27, "D4 is the firmware's status LED on IO2 (off: disabled, on: enabled, blinking: driver fault); "
                         "a genuine DevKitC has no LED there. The LED and R8 keep IO2 low at boot, as it must be."),
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    ("C1", "C", "100nF", "rig:C_0805_2012Metric_Pad1.18x1.45mm_HandSolder", {"1": "+5V", "2": "GND"}, C100N,
     (139.7, 88.9), {}),
    ("J1", "Conn_01x03", "to controller J4", "rig:Wire_Pads_1x03_P2.54mm",
     {"1": "+5V", "2": "GND", "3": "HALL_OUT"}, hand("3-wire cable soldered in (or a 1x3 pin header)"),
     (170.18, 88.9), {}),
]
HALL_FLAGS = [("+5V", 76.2, 66.04), ("GND", 88.9, 66.04)]
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

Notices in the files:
README.md:
license: MIT
